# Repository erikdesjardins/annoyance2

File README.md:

# annoyance2

Digital musical tesla coil interrupter

Digital version of https://github.com/erikdesjardins/annoyance. Intended to run on a "blue pill" [STM32F103C8](https://www.st.com/resource/en/datasheet/stm32f103c8.pdf) board.

## Setup

Add the target corresponding to Cortex-M3:

```sh
rustup target add thumbv7m-none-eabi
```

Install tools for linking/flashing:

```sh
cargo install flip-link probe-run
```

Follow `probe-rs` docs to install drivers for flashing:

https://probe.rs/docs/getting-started/probe-setup/

## Development

### Run on device

```sh
# use `debug` or `trace` for more info
set DEFMT_LOG=info

cargo run --manifest-path firmware/Cargo.toml --target thumbv7m-none-eabi
```

### Run with visualizer

```sh
cargo run --manifest-path firmware/Cargo.toml --target thumbv7m-none-eabi --release | cargo run --manifest-path visualizer/Cargo.toml --release
```

### Misc

```sh
cargo objdump --target thumbv7m-none-eabi --release -- --disassemble --no-show-raw-insn --print-imm-hex

cargo objdump --target thumbv7m-none-eabi --release -- --disassemble --no-show-raw-insn --print-imm-hex --disassemble-symbols=USART1
```

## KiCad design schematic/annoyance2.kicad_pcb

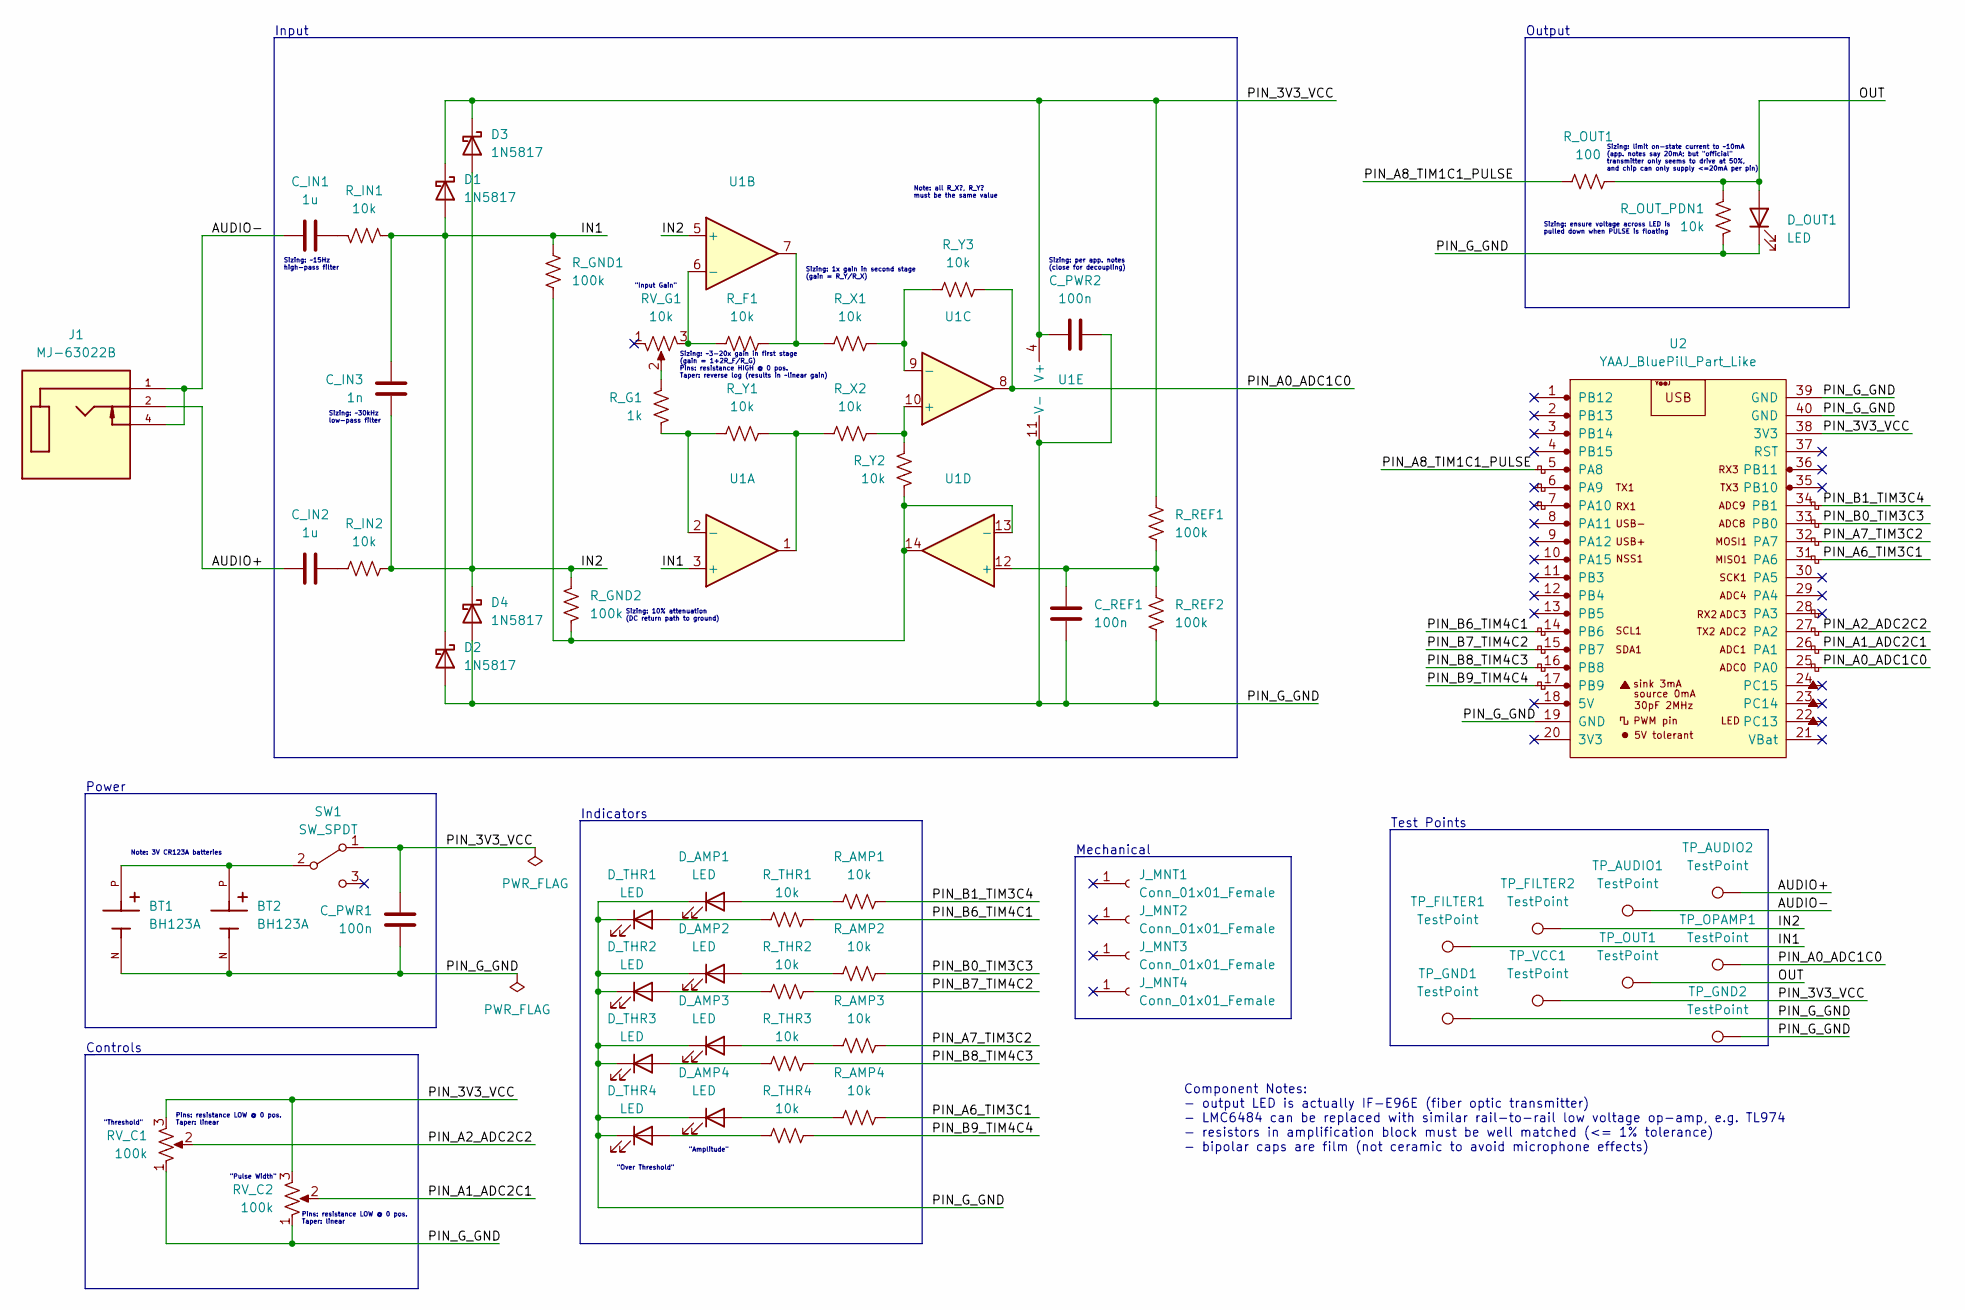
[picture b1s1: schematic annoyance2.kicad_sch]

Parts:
BT1, BT2: BH123A; BAT_BH123A; PARTREV E
C_IN1, C_IN2: 1u; C_Rect_L7.2mm_W5.5mm_P5.00mm_FKS2_FKP2_MKS2_MKP2
C_IN3: 1n; C_Rect_L7.2mm_W2.5mm_P5.00mm_FKS2_FKP2_MKS2_MKP2
C_PWR1, C_PWR2: 100n; C_Rect_L7.2mm_W2.5mm_P5.00mm_FKS2_FKP2_MKS2_MKP2
C_REF1: 100n; C_Rect_L7.2mm_W2.5mm_P5.00mm_FKS2_FKP2_MKS2_MKP2
D1, D2, D3, D4: 1N5817; D_DO-41_SOD81_P10.16mm_Horizontal
D_AMP1, D_AMP2, D_AMP3, D_AMP4: LED; LED_D5.0mm
D_OUT1: LED; IF-E96E
D_THR1, D_THR2, D_THR3, D_THR4: LED; LED_D5.0mm
J1: MJ-63022B; CUI_MJ-63022B; PARTREV 1.0
J_MNT1, J_MNT2, J_MNT3, J_MNT4: Conn_01x01_Female; MountingHole_3.2mm_M3_Pad
RV_C1, RV_C2: 100k; TRIM_PT01-D125D-B103
RV_G1: 10k; TRIM_PT01-D130D-A103
R_AMP1, R_AMP2, R_AMP3, R_AMP4: 10k; R_Axial_DIN0204_L3.6mm_D1.6mm_P5.08mm_Horizontal
R_F1: 10k; R_Axial_DIN0204_L3.6mm_D1.6mm_P5.08mm_Horizontal
R_G1: 1k; R_Axial_DIN0204_L3.6mm_D1.6mm_P5.08mm_Horizontal
R_GND1, R_GND2: 100k; R_Axial_DIN0204_L3.6mm_D1.6mm_P5.08mm_Horizontal
R_IN1, R_IN2: 10k; R_Axial_DIN0204_L3.6mm_D1.6mm_P5.08mm_Horizontal
R_OUT1: 100; R_Axial_DIN0204_L3.6mm_D1.6mm_P5.08mm_Horizontal
R_OUT_PDN1: 10k; R_Axial_DIN0204_L3.6mm_D1.6mm_P5.08mm_Horizontal
R_REF1, R_REF2: 100k; R_Axial_DIN0204_L3.6mm_D1.6mm_P5.08mm_Horizontal
R_THR1, R_THR2, R_THR3, R_THR4: 10k; R_Axial_DIN0204_L3.6mm_D1.6mm_P5.08mm_Horizontal
R_X1, R_X2: 10k; R_Axial_DIN0204_L3.6mm_D1.6mm_P5.08mm_Horizontal
R_Y1, R_Y2, R_Y3: 10k; R_Axial_DIN0204_L3.6mm_D1.6mm_P5.08mm_Horizontal
SW1: SW_SPDT; OS102011MA1Q
TP_AUDIO1, TP_AUDIO2: TestPoint; TestPoint_THTPad_2.0x2.0mm_Drill1.0mm
TP_FILTER1, TP_FILTER2: TestPoint; TestPoint_THTPad_2.0x2.0mm_Drill1.0mm
TP_GND1, TP_GND2: TestPoint; TestPoint_THTPad_2.0x2.0mm_Drill1.0mm
TP_OPAMP1: TestPoint; TestPoint_THTPad_2.0x2.0mm_Drill1.0mm
TP_OUT1: TestPoint; TestPoint_THTPad_2.0x2.0mm_Drill1.0mm
TP_VCC1: TestPoint; TestPoint_THTPad_2.0x2.0mm_Drill1.0mm
U1: (no value)
U2: YAAJ_BluePill_Part_Like; YAAJ_BluePill_1

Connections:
/AUDIO+: C_IN2.1, J1.2, TP_AUDIO2.1
/AUDIO-: C_IN1.1, J1.1, J1.4, TP_AUDIO1.1
/IN1: C_IN3.2, D1.2 (A), D2.1 (K), R_GND1.1, R_IN1.1, TP_FILTER1.1, U1.3 (+)
/IN2: C_IN3.1, D3.2 (A), D4.1 (K), R_GND2.1, R_IN2.2, TP_FILTER2.1, U1.5 (+)
/OUT: D_OUT1.2 (A), R_OUT1.2, R_OUT_PDN1.2, TP_OUT1.1
/PIN_3V3_VCC: C_PWR1.2, C_PWR2.1, D1.1 (K), D3.1 (K), RV_C1.3, RV_C2.3, R_REF1.1, SW1.1 (A), TP_VCC1.1, U1.4 (V+), U2.38 (3V3)
/PIN_A0_ADC1C0: R_Y3.2, TP_OPAMP1.1, U1.8, U2.25 (PA0)
/PIN_A1_ADC2C1: RV_C2.2, U2.26 (PA1)
/PIN_A2_ADC2C2: RV_C1.2, U2.27 (PA2)
/PIN_A6_TIM3C1: R_AMP4.2, U2.31 (PA6)
/PIN_A7_TIM3C2: R_AMP3.2, U2.32 (PA7)
/PIN_A8_TIM1C1_PULSE: R_OUT1.1, U2.5 (PA8)
/PIN_B0_TIM3C3: R_AMP2.2, U2.33 (PB0)
/PIN_B1_TIM3C4: R_AMP1.2, U2.34 (PB1)
/PIN_B6_TIM4C1: R_THR1.2, U2.14 (PB6)
/PIN_B7_TIM4C2: R_THR2.2, U2.15 (PB7)
/PIN_B8_TIM4C3: R_THR3.2, U2.16 (PB8)
/PIN_B9_TIM4C4: R_THR4.2, U2.17 (PB9)
/PIN_G_GND: BT1.N, BT2.N, C_PWR1.1, C_PWR2.2, C_REF1.1, D2.2 (A), D4.2 (A), D_AMP1.1 (K), D_AMP2.1 (K), D_AMP3.1 (K), D_AMP4.1 (K), D_OUT1.1 (K), D_THR1.1 (K), D_THR2.1 (K), D_THR3.1 (K), D_THR4.1 (K), RV_C1.1, RV_C2.1, R_OUT_PDN1.1, R_REF2.2, TP_GND1.1, TP_GND2.1, U1.11 (V-), U2.19 (GND), U2.39 (GND), U2.40 (GND)
unnamed: BT1.P, BT2.P, SW1.2 (B)
unnamed: C_IN1.2, R_IN1.2
unnamed: C_IN2.2, R_IN2.1
unnamed: C_REF1.2, R_REF1.2, R_REF2.1, U1.12 (+)
unnamed: D_AMP1.2 (A), R_AMP1.1
unnamed: D_AMP2.2 (A), R_AMP2.1
unnamed: D_AMP3.2 (A), R_AMP3.1
unnamed: D_AMP4.2 (A), R_AMP4.1
unnamed: D_THR1.2 (A), R_THR1.1
unnamed: D_THR2.2 (A), R_THR2.1
unnamed: D_THR3.2 (A), R_THR3.1
unnamed: D_THR4.2 (A), R_THR4.1
unnamed: RV_G1.2, R_G1.2
unnamed: RV_G1.3, R_F1.1, U1.6 (-)
unnamed: R_F1.2, R_X1.1, U1.7
unnamed: R_G1.1, R_Y1.1, U1.2 (-)
unnamed: R_GND1.2, R_GND2.2, R_Y2.1, U1.13 (-), U1.14
unnamed: R_X1.2, R_Y3.1, U1.9 (-)
unnamed: R_X2.1, R_Y1.2, U1.1
unnamed: R_X2.2, R_Y2.2, U1.10 (+)

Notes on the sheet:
Component Notes: - output LED is actually IF-E96E (fiber optic transmitter) - LMC6484 can be replaced with similar rail-to-rail low voltage op-amp, e.g. TL974 - resistors in amplification block must be well matched (<= 1% tolerance) - bipolar caps are film (not ceramic to avoid microphone effects)
Sizing: ~30kHz low-pass filter
"Over Threshold"
Controls
"Threshold"
Pins: resistance LOW @ 0 pos. Taper: linear
Input
Power
Sizing: limit on-state current to ~10mA (app. notes say 20mA; but "official" transmitter only seems to drive at 50%, and chip can only supply <=20mA per pin)
Output
Mechanical
Sizing: ensure voltage across LED is pulled down when PULSE is floating
Test Points
Indicators
Sizing: ~3-20x gain in first stage (gain = 1+2R_F/R_G) Pins: resistance HIGH @ 0 pos. Taper: reverse log (results in ~linear gain)
Sizing: ~15Hz high-pass filter
"Amplitude"
Sizing: 1x gain in second stage (gain = R_Y/R_X)
Note: all R_X?, R_Y? must be the same value
"Pulse Width"
Sizing: 10% attenuation (DC return path to ground)
Note: 3V CR123A batteries
"Input Gain"
Sizing: per app. notes (close for decoupling)

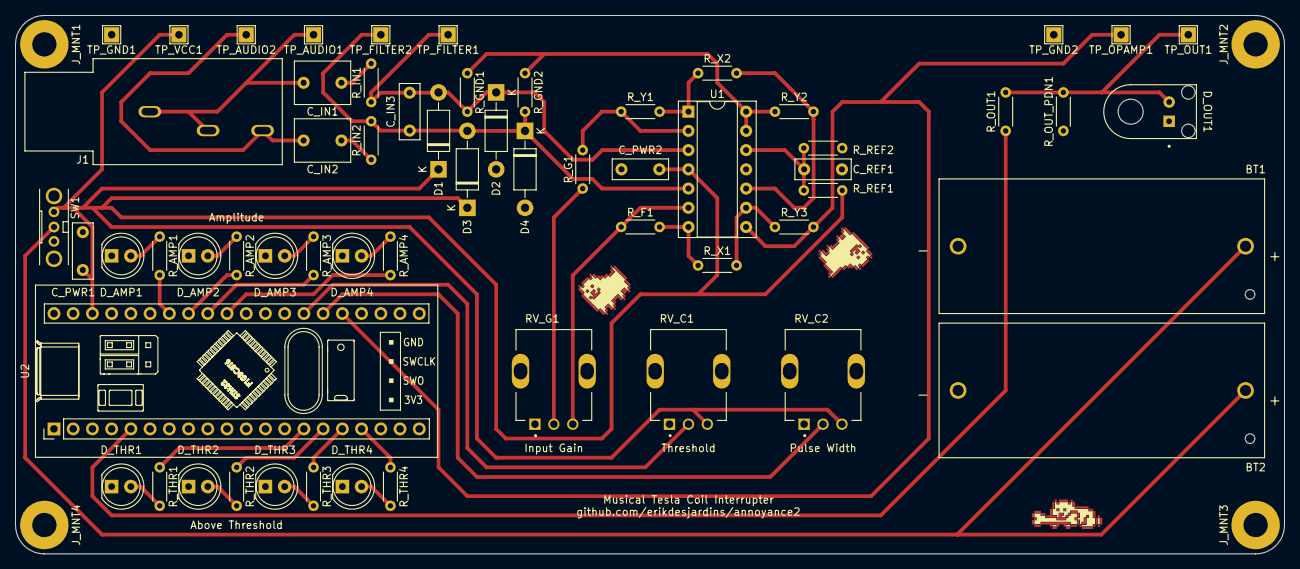
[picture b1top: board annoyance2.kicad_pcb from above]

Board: 2 copper layers, 167.6 x 71.1 mm, 64 parts (0 on the bottom side), 39 nets.

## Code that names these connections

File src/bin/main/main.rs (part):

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        let mut adc1 = Adc::adc1(cx.device.ADC1, clocks);
        adc1.set_sample_time(config::adc::SAMPLE);

        let adc1_ch0: pins::A0_ADC1C0 = gpioa.pa0.into_analog(&mut gpioa.crl);

        let adc1_dma = adc1.with_dma(adc1_ch0, dma1_ch1);

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
        let adc2_controls = Adc::adc2(cx.device.ADC2, clocks);

        let threshold_control_pin: pins::A2_ADC2C2 = gpioa.pa2.into_analog(&mut gpioa.crl);
        let pulse_width_control_pin: pins::A1_ADC2C1 = gpioa.pa1.into_analog(&mut gpioa.crl);

        defmt::info!("Configuring amplitude indicator timer...");

        let tim3_ch4: pins::B1_TIM3C4 = gpiob.pb1.into_alternate_push_pull(&mut gpiob.crl);
        let tim3_ch3: pins::B0_TIM3C3 = gpiob.pb0.into_alternate_push_pull(&mut gpiob.crl);
        let tim3_ch2: pins::A7_TIM3C2 = gpioa.pa7.into_alternate_push_pull(&mut gpioa.crl);
        let tim3_ch1: pins::A6_TIM3C1 = gpioa.pa6.into_alternate_push_pull(&mut gpioa.crl);

        let mut amplitude_timer = Timer::new(cx.device.TIM3, &clocks).pwm_hz(
            (tim3_ch1, tim3_ch2, tim3_ch3, tim3_ch4),
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
        defmt::info!("Configuring threshold indicator timer...");

        let tim4_ch1: pins::B6_TIM4C1 = gpiob.pb6.into_alternate_push_pull(&mut gpiob.crl);
        let tim4_ch2: pins::B7_TIM4C2 = gpiob.pb7.into_alternate_push_pull(&mut gpiob.crl);
        let tim4_ch3: pins::B8_TIM4C3 = gpiob.pb8.into_alternate_push_pull(&mut gpiob.crh);
        let tim4_ch4: pins::B9_TIM4C4 = gpiob.pb9.into_alternate_push_pull(&mut gpiob.crh);

        let mut threshold_timer = Timer::new(cx.device.TIM4, &clocks).pwm_hz(
            (tim4_ch1, tim4_ch2, tim4_ch3, tim4_ch4),
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
        defmt::info!("Configuring pulse output timer...");

        let tim1_ch1: pins::A8_TIM1C1_PULSE = gpioa.pa8.into_alternate_push_pull(&mut gpioa.crh);

        let pulse_timer =
            OneshotTimer::new(cx.device.TIM1, &clocks).one_pulse_mode(tim1_ch1, &mut afio.mapr);
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
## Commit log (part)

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2022-05-09 add link to old project in readmo
2022-05-09 initial setup from defmt-app-template
2022-05-09 set log level in development
2022-05-13 configure clocks how i expect them to be used
2022-05-13 add objdump command
2022-05-16 read from adc via dma
2022-05-16 set indicator LED initially off
2022-05-18 implement fft
2022-05-19 use blackman-harris window
2022-05-19 put blackman-harris filter coefficients in ram
2022-05-20 extract phase and frequency of maximum amplitude bin
2022-05-25 tweak copying samples from input to scratch buffer
2022-05-25 make fft amplitude/phase calculation faster and more precise
2022-05-25 switch iterator chain to for loop
2022-05-25 move config options into submodules
2022-05-25 enable clippy::cast_lossless
2022-05-26 enable clippy lints related to cast/truncation and fix issues
2022-05-26 add debug logging for last few samples
2022-05-26 fix frequency binning calculation with complex fft samples
2022-05-26 tweak ADC sample rate
    ~4x lower ADC clock, slightly higher sample rate
    i hypothesize that a lower ADC clock will improve accuracy, but it's hard to tell
2022-05-26 switch protection diodes out for schottkys, per app. notes
2022-05-26 remove debug logging of final samples
    it's not that useful, now that i know it is in fact copying data correctly
2022-05-28 silence, clippy
2022-05-28 halve sampling rate to ~20kHz per channel
    we don't want to reproduce frequencies above 10kHz anyways
2022-05-28 fix phase calculation
    turns out you can't just add a constant offset to convert -pi..pi to 0..2pi
2022-05-28 make amplitude_squared even more rigorously check for overflow
2022-05-28 add debug flag to control logging timing information
2022-05-28 use consts for generated array lengths
2022-05-28 remove config options for logging and just use log levels
2022-05-28 dump config to log on startup
2022-05-28 halve fft size again
    need this to fit oversampling buffer in memory
2022-05-28 move debug flags to separate file
    this should make it harder to accidentally commit flips of debug flags when there are other (desired) config changes
2022-05-29 reimplement fft (now it actually works!)
2022-05-29 tweak twiddle factors--store sin table instead to save 1/4 bytes
2022-05-29 audit window functions
2022-05-29 add ability to set phase of fake input, and use cos instead of sin
    looks like the fft bases its initial phase on cos
    this works better for us anyways, since we want to trigger the coil to fire on peaks, and cos peaks at 0 phase, which is perfect
    while testing this, i can tell that the phase calculation is correct-ish -- shifting the phase by pi/2 at a time does shift the resulting phase
    BUT, there seems to be a constant ~40deg offset, which is weird...
    thankfully a constant offset shouldn't impact the functioning of this device -- it may result in different frequencies being in different relative phases compared to each other, but i don't think the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
2022-05-29 physically separate ADC pins, put pwm reference between them
    injection current in adjacent pins can negatively affect the adc; leaving a gap between pins will help mitigate this
    noise from nearby pwms can impact the adc as well; putting the pwm in the middle should ensure that both channels are equally impacted (and hence cancelled out in the difference)
2022-05-29 add smoothing caps on reference voltage and across the rails, change back to 10k on voltage reference
2022-05-29 add explicit constant for scale
    to make sure we don't forget to change the twiddle factor scaling if we ever change this to i32
2022-05-29 add component notes to schematic
2022-05-30 keep fixed point values in `fixed` types when returning
    this is less error prone, and makes it obvious which bits are fractional bits
2022-05-30 explain why we expect adc difference truncation to always fit
2022-05-30 tweak fixed point again: only expose whole number values or integer-representation scaling factors
    this will fit into upcoming code better, especially for `phase`
    also, the changes to `amplitude_sqrt` make related code simpler (no need to mask out fractional bits in callers), and the rename should prevent misuse
2022-05-31 use debug-mode checked truncation
2022-05-31 frequency adjustment: avoid rounding twice
    this gets us _even closer_ to linearity
2022-05-31 find up to 8 peak frequencies
2022-06-02 use properly-rounded integer division for "truncating" divisions
    this makes frequency adjustments and oversampling averaging more accurate
2022-06-02 fix adc conversion time calculation (fixing frequencies being off by ~25%)
    needed to include an additional 12.5 cycles for successive approximation
    always read the fine print...
2022-06-02 adjust adc sample rate back up to ~40kHz, after accounting for additional 12.5 cycles latency
2022-06-02 enable 2x oversampling
    this doesn't really seem necessary (there isn't noticeably less noise when enabling this, and the signal is pretty clean already)
    but why not. it only costs ~1k
2022-06-03 move fft peak logging behind a debug flag
    we'll want to disable this when testing other things, since it's quite spammy
2022-06-06 consolidate `fixed`/`num` modules into `math`, make `scale_by` a trait
2022-06-07 clean up peak computations a bit by using `Vec` more and guaranteeing size consistency
2022-06-07 add debugging option to log all pulses
2022-06-15 tweak layout of filtering caps on schematic
2022-06-16 fix timer enabling
    (TIM1 needs the AOE automatic output enable bit set)
2022-06-17 add analog preamplification stage
    the input amplitude from a guitar (or even a headphone jack) is just too low to reliably detect.
    i wanted to avoid this for circuit complexity reasons, but it's (unfortunately? fortunately?) necessary
    this does have some major benefits though--
    first, the instrumentation amplifier naturally converts the differential input to single-ended, allowing us to halve the input buffer size and avoid doing the differential subtraction in software
    second, this lets us use a real buffer for the virtual ground, which should be much more stable than filtered pwm
    third, this gives us easily adjustable gain, which is useful, and avoids the question of how exactly to tune
2022-06-18 add symbol/footprint for devboard, add batteries, reverse log pot (and control pots), etc.
2022-06-22 add indicator LEDs
2022-06-22 add one more power filtering cap
2022-06-22 tweak more tracks
2022-06-23 add mounting holes and round pcb corners
2022-06-24 tweak more traces
2022-06-24 remove center mounting hole
    it's quite ugly, and it's not necessary
    if we need physical support under the middle of the board, we can just put a support there without going through the board--
    we'll have enough horizontal positioning from the corner mounting points
2022-06-29 properly segment a branching track
    (this helps the track rounding plugin work properly)
2022-07-04 tweak some more track connections to work better with track rounding
2022-07-05 power consumption: use 10k pots for adjustments
    (these could even be 100k, but i only ordered 1k and 10k pots...)
2022-07-05 power consumption: remove output pullup, make pulldown much larger
    the "official" interrupter doesn't have a pullup; it's hard to tell whether it actually makes the output switch faster; and it draws power continuously
2022-07-07 power consumption: 100k resistors on Vcc/2 voltage reference
2022-07-07 power consumption: 100k adjustment pots
2022-07-13 use max sample value as default fake input amplitude
2022-07-13 placate clippy
2022-07-20 fix amplitude indicator calculation
2022-07-20 implement handling of controls for amplitude threshold and pulse width
2022-07-20 reduce cpu clock from 72 MHz to 24 MHz
    this greatly reduces power consumption, since most of the power during operation is consumed by the micro
2022-07-20 1.0.0
2022-07-22 ensure adjusted frequency is not zero
    this avoids a divide-by-zero panic
2022-07-22 improve scheduling consistency, cancel any inflight pulse when swapping buffers
2022-07-22 increase scheduling offset / holdoff to 50us to avoid popping
    when this is too low, pulses can get scheduled too close together
    which effectively creates one long pulse, causing a higher-amplitude pop
2022-07-23 update deps
2022-07-24 use dedicated ScalingFactor type instead of passing around raw numbers
2022-07-24 reuse Peak::period instead of reimplementing it
2022-07-24 add assertion for adc precision < 16bits assumption
2022-07-25 improve timing logs
2022-07-25 adjust frequency back up to 48MHz
    this is enough to avoid any overruns, even with ...strenuous... inputs
    it also brings the max possible fft frequency down a bit, to about C8 (roughly the highest note a violin can play in the extreme)
    we really don't want to be reproducing anything higher than that
2022-08-04 switch to rail-to-rail opamp
    3V is such a low supply voltage that we need all the range we can get
    the TLC074 and similar op-amps are unable to use something on the order of 0.7V of the supply span, which is huge at 3V
2022-08-07 rename `BUF_LEN_COMPLEX / 2` -> `BUF_LEN_COMPLEX_REAL`
2022-08-08 add scaffolding for FFT amplitude equalization
2022-08-08 implement FFT amplitude equalization
    this seems like it shouldn't be necessary...it's quite hard to search for, but i can't find anyone else mentioning a non-flat frequency response from an FFT
    and it doesn't make sense--it would make extracting amplitudes from an FFT meaningless if there was some falloff at high frequencies
    (i would at least expect one of the FFT implementation papers i've seen to mention correcting for this, if it is a thing)
    note for posterity: this happens even with a generated input with no window function. so it really seems like a problem specifically with the FFT, and not with anything else
    (there is about 10% attenuation at 4kHz vs. 40Hz, from the input filtering,
2022-09-22 switch to collecting all peaks in a buffer
    to enable easier experimentation, e.g. with combining harmonics together
2022-09-23 display and tweak computation of MAX_SCRATCH_PEAKS in config
2022-12-11 gitignore todo.txt
2022-12-11 strip visualizer
2022-12-12 format on save in vs code; remove unnecessary config now that we don't use a lib crate
2022-12-12 visualizer: don't start drawing until we see our first line of input
2022-12-12 visualizer: remove unnecessary polling timeout
    we can just block on this event, since this is a separate thread anyways
2022-12-13 visualizer: only exit on ctrl-c
    pressing q gets me in the habit of trying to exit other stuff with it, which then gets written to my next command, which is annoying
2022-12-13 firmware: adapt adc and fft debug logging to visualizer format
2022-12-13 visualizer: allow multiple charts, greatly improve parsing
2022-12-13 add readme example for running with visualizer
2022-12-13 enable debug symbols in bench builds (for external profiling)
2022-12-20 1.1.1
2022-12-22 visualizer: use braille markers
    this looks _way_ better
2023-03-31 optimize pulse firing--avoid setting pulse width every time
    since the autoreload register keeps its value,
    we only need to change it when fetching a new value from the control
2023-03-31 fix cargo-objdump invocation
2023-04-01 don't offset start of each pulse by 1 period
    i assume i did this in case the phase offset is 0 (causing a pulse immediately), but
    - there is already protection for a pulse coming too soon in `next_pulse()`
    - this causes us to skip the first pulse every buffer swap, which causes audible weirdness with low frequencies (at least i think this is the cause, haven't tested it yet)
2023-04-01 somewhat optimize next_pulse
    this _might_ go from ~13.5us avg to ~12.5us avg, and/or might slightly reduce the cost when adjusting for a too-short interval, but it's quite hard to tell
    it's surprisingly hard to optimize this function, especially given how...nonoptimal the previous implementation is (accumulating an `Option<(Duration, Instant)>`!)
2023-04-02 cleanup to_value_in_range_via by implementing ScaleBy for durations
2023-05-13 cull peaks below minimum frequency
